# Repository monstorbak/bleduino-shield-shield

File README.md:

BLEduino Shield-Shield
===========================
Here you'll find all of the hardware design files related to the BLEduino's Shield-Shield.

* Bill of Materials - The parts list used on the BLEduino Shield-Shield.  Part type, mount, pads, etc.
* Eagle - Schematic and PCB files for the BLEduino Shield-Shield.
* Gerber - All of the Gerber files needed to produce your own Shield-Shields.
* PDFs - PDF copies of the schematics and pcb including the individual layers.

These files are licensed under a [Creative Commons Attribution Share-Alike license](http://creativecommons.org/licenses/by-sa/2.5/).  That means you're allowed to modify, view, distribute, and remix any of the files for personal and comerical purposes as long as you credit the BLEduino and release your design files under the same or similar license.

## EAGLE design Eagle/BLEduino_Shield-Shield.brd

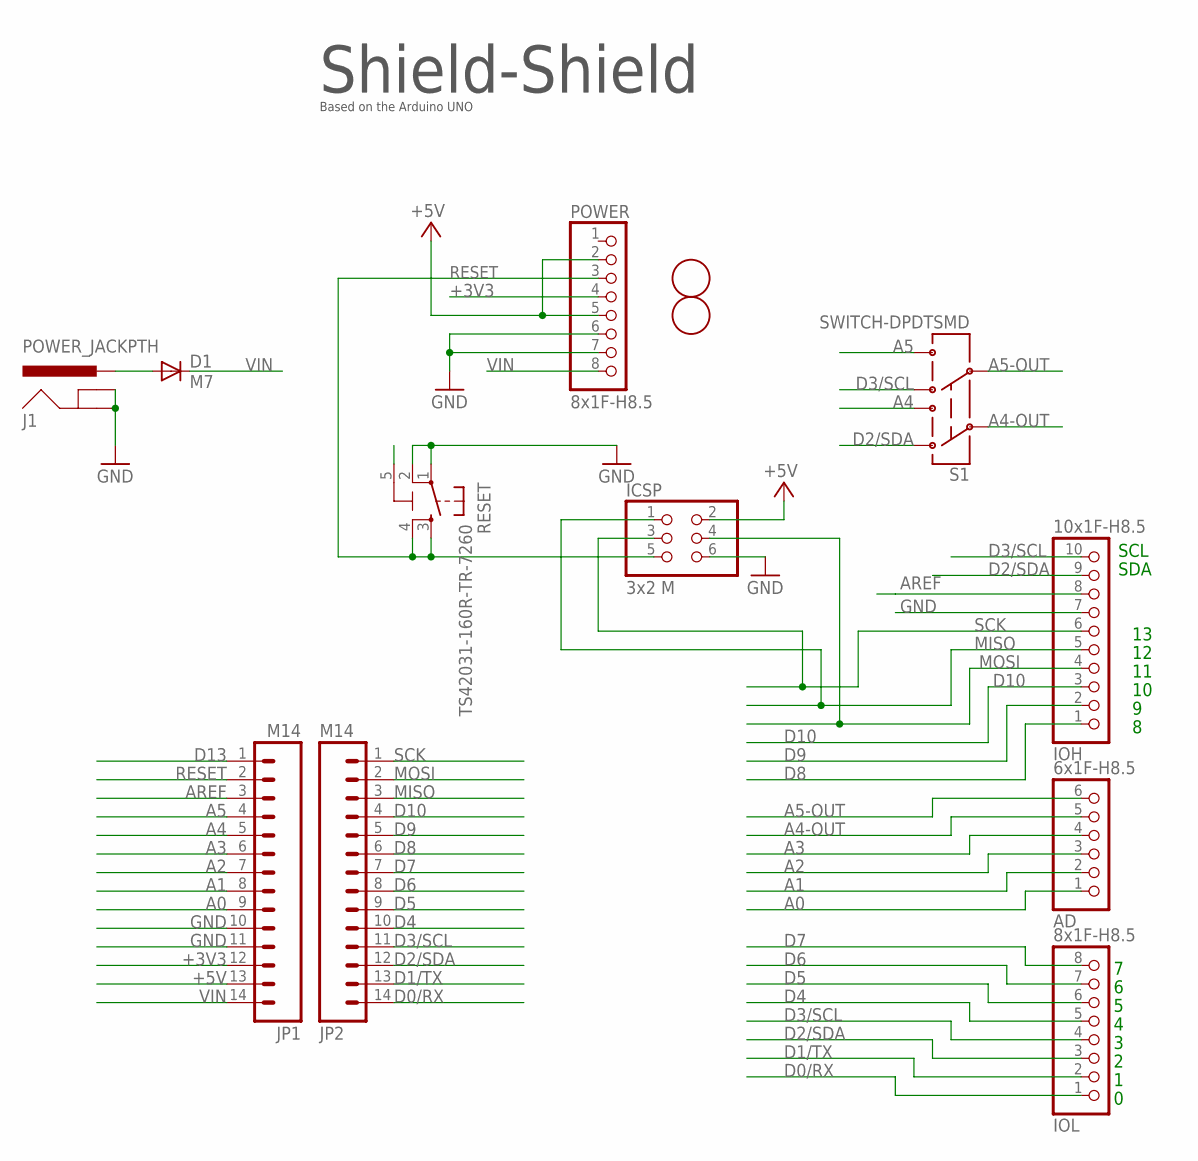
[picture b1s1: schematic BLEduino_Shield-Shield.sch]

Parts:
AD: 6x1F-H8.5; 1X06
D1: M7; SMB
FD1, FD2: FIDUCIALMOUNT; FIDUCIA-MOUNT
ICSP: 3x2 M; 2X03
IOH: 10x1F-H8.5; 1X10
IOL: 8x1F-H8.5; 1X08
J1: POWER_JACKPTH; POWER_JACK_PTH
JP1, JP2: M14; 1X14
POWER: 8x1F-H8.5; 1X08
RESET: TS42031-160R-TR-7260; TS42
S1: SWITCH-DPDTSMD; AYZ0202

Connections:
+3V3: JP1.12, POWER.4
+5V: ICSP.2, JP1.13, POWER.2, POWER.5
A0: AD.1, JP1.9
A1: AD.2, JP1.8
A2: AD.3, JP1.7
A3: AD.4, JP1.6
A4: JP1.5, S1.3
A4-OUT: AD.5, S1.2
A5: JP1.4, S1.6
A5-OUT: AD.6, S1.5
AREF: IOH.8, JP1.3
D0/RX: IOL.1, JP2.14
D1/TX: IOL.2, JP2.13
D2/SDA: IOH.9, IOL.3, JP2.12, S1.1
D3/SCL: IOH.10, IOL.4, JP2.11, S1.4
D4: IOL.5, JP2.10
D5: IOL.6, JP2.9
D6: IOL.7, JP2.8
D7: IOL.8, JP2.7
D8: IOH.1, JP2.6
D9: IOH.2, JP2.5
D10: IOH.3, JP2.4
D13: JP1.1
GND: ICSP.6, IOH.7, J1.GND, J1.GNDBREAK, JP1.10, JP1.11, POWER.6, POWER.7, RESET.1, RESET.2
MISO: ICSP.1, IOH.5, JP2.3
MOSI: ICSP.4, IOH.4, JP2.2
unnamed: D1.A, J1.PWR
RESET: ICSP.5, JP1.2, POWER.3, RESET.3, RESET.4
SCK: ICSP.3, IOH.6, JP2.1
VIN: D1.C, JP1.14, POWER.8

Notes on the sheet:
SDA
SCL
Shield-Shield
Based on the Arduino UNO

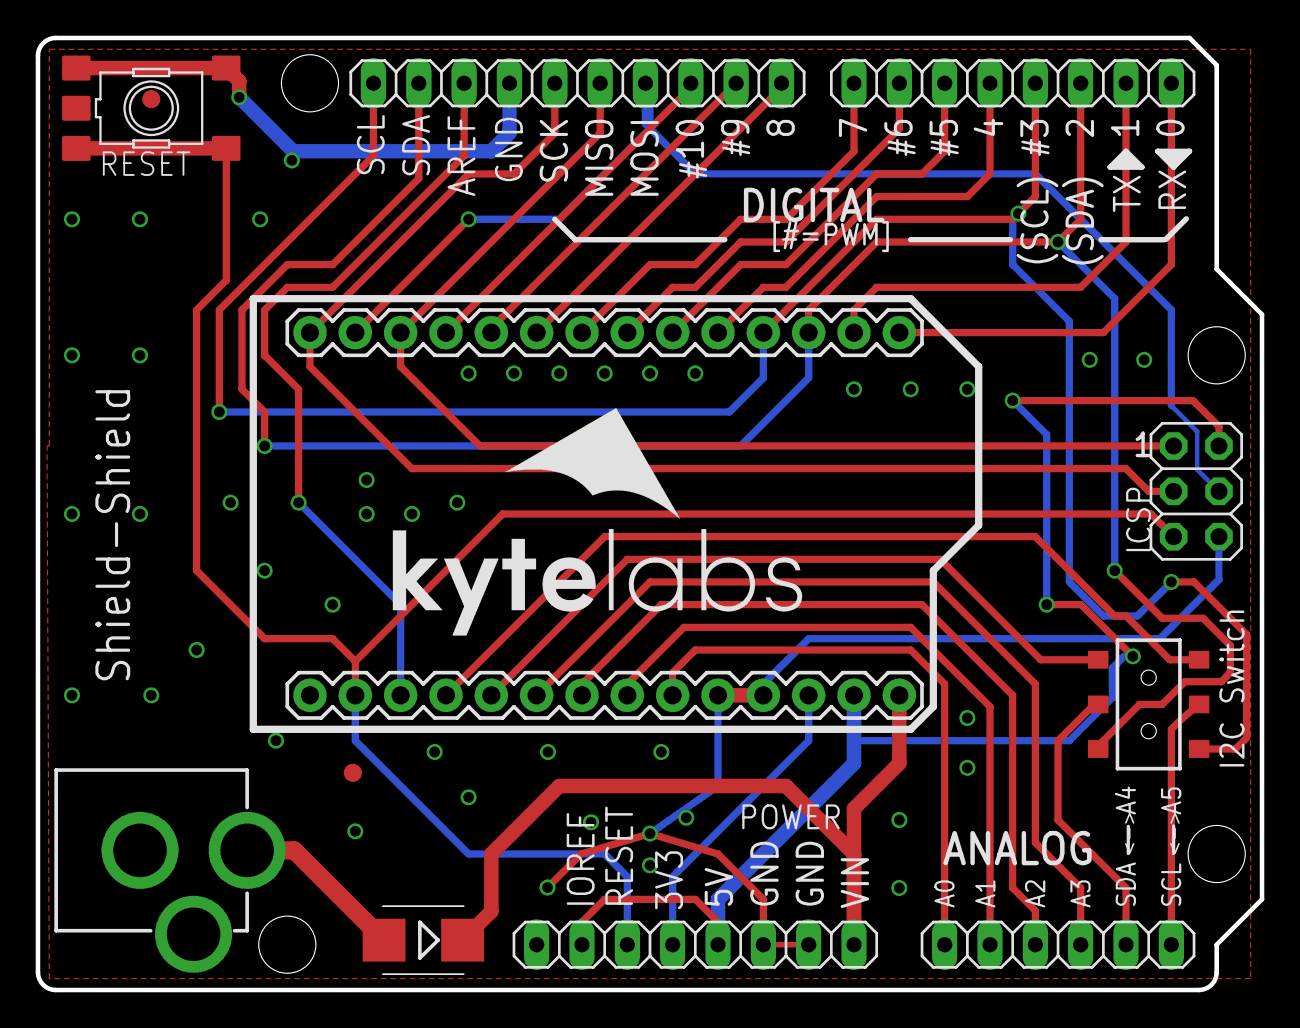
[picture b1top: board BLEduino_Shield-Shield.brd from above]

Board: 4 copper layers, 68.6 x 53.3 mm, 14 parts (0 on the bottom side), 29 nets.

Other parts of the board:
U$1: KYTELABS_LOGO_BIG

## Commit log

2013-10-01 First Shield-Shield hardware source commit
2013-10-01 Updated the Readme
2013-10-01 Fixed a heading problem on the README

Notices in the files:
parts and their libraries:
SparkFun: Licensing: CC v3.0 Share-Alike You are welcome to use this library for commercial purposes.
